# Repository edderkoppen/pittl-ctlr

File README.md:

# pittl-ctlr
Raspberry Pi TTL Controller, 0.2.0  
nGelwan | 2019

## Introduction
PiTTL is a collection of schematics and code which can be used to cheaply build a remotely-controllable random TTL sequence generator using a Raspberry Pi 4 (https://www.raspberrypi.org/products/raspberry-pi-4-model-b/) and a couple of additional hardware components. It consists of two parts, the PiTTL controller, contained in this repository, and the PiTTL client (https://github.com/extradosages/pittl-client). When pushed to the extreme, PiTTL supports generating sequences which run for at least a month consisting of pulses of less than 10ms duration. 

## Installation
### HAT Construction
If you don't have an already constructed PiTTL, one can be constructed relatively cheaply. The hardware for PiTTL has been designed like a Raspberry Pi HAT (https://www.raspberrypi.org/blog/introducing-raspberry-pi-hats/), to live on an auxiliary baord which talks to the Raspberry Pi via its GPIO headers. The schematics for the HAT are detailed in the **board** sub-repo (https://github.com/extradosages/pittl-ctlr/board), and can be viewed with EDA software. I used Eagle (https://www.autodesk.com/products/eagle/overview). The gerber files packaged in the **board** sub-repo can be supplied to a custom PCB-vendor in order to custom print the PCB for the HAT.

### Software Installation
One may install the PiTTL controller software on any Raspberry Pi, although the software has only been tested with the Raspberry Pi 4, and the practical limitation of the TTL driver listed above are given in the context of the hardware on a Raspberry Pi 4. Presumably, the software will function on a variety of operating systems, but certain features have been designed with Raspbian in mind (e.g. automatic start using systemd).

The only software prerequisites for the installation of pittld are python >=3.4, python setuptools, and a C-compiler for the compilation of pigpio. To setup and install the software, a very rudimentary shell script *setup/setup.sh* is provided, which should be run as root. Be warned, the setup script is non-transactional and doesn't try very hard to catch errors, so one should pay attention closely to stdout during the installation. If setup completes successfully, pittld may be started by entering

>*pittld*

at the command-line or-- assuming the installation of the systemd units succeeded-- automatically upon restart of the Raspberry Pi. The logs for pittld can be followed with  

>*journalctl -f -u pittld*

on Raspbian. Confirmation that pittld is running successfully can be found in journalctl or by observing updates on the HAT's LCD.

## Overview
### Usage
PiTTL can be used to stage and then generate individual sequences of TTL pulses, called **programs**. Generating-- also known as **staging**-- a program is a two-step process: first, the **timing** of the program is staged, and then the program's **sequence** is staged. If a sequence has been successfully staged, a program can be **started** and **stopped** at will.

**Timing** is specified with 3 parameters: the **total time**, **exposure fraction**, and **resolution**. Total time is the desired length of the program, exposure fraction is the desired fraction of the program during which TTL-on logic will occur, and resolution is the minimum width of a TTL-on pulse. The resolution parameter is *very* important. It drastically simplifies the algorithm for generating random sequences of pulses satisfying the desired exposure fraction. It is important to note that when these three parameters are supplied to PiTTL, that total time and exposure fraction will be adjusted so that the time spent in TTL-on and TTL-off are both integer multiples of the resolution, and so that they are as close to the values specified as possible. Thus, after staging, timing is converted into the **specified**, **adjusted**, and **digital** domains. The specified timing consists of those floating point values requested, adjusted are those values after adjustment for resolution, and digital are those values in integral units of resolution.

A **sequence** is literally a binary sequence representing the TTL-logic time-series of the program. PiTTL can be induced to randomly generate a sequence based on any valid staged timing. If a sequence has been staged and new timing is then staged, the two are then unrelated, and the staged sequence is purged.

Once a program has been **started**, the timing and the sequence are considered **committed**. New sequences and timing can be staged without interrupting the running program.

PiTTL is capable of evaluating the **progress** and **ETA** of a currently running program, and also **stopping** a program, clearing any committed timings and sequences.

This functionality is implemented via PiTTL controller's python API and publicly via the combination of the PiTTL controller's manager service and the PiTTL client (https://github.com/extradosages/pittl-client).

### Details
The PiTTL controller is organised into several related hardware components and software services. These are the:
1. Manager
2. TTL Driver
3. LCD
4. Connectivity monitor

The software services are packaged under the name **pittld**, for PiTTL Daemon.
#### The Manager
The manager provides a public endpoint for communicating with a PiTTL controller. It is the means by which a PiTTL client can command a PiTTL controller to stage timing and sequences and to start and stop programs, and also the means by which a PiTTL client can query a PiTTL controller for any staged or committed timing or sequences, or the progress of any running program.
#### The TTL Driver
This software service leverages the use of the python library PiGPIO (http://abyz.me.uk/rpi/pigpio/) and a MOSFET to generate the ~4.4V square wave pulses consituting a TTL pulse train.

This software includes the routines to approximately sample from the collection of all subsets of the unit interval with fixed measure without measure-zero components. A resolution parameter (defining the minimum width of a sampled pulse) specifies the accuracy (and memory burden) of the sampling routine, with asymptotic convergence to the ideal sampler upon decreasing the parameter. Once sampled, such a subset defines a pulse train via a mapping of the unit interval onto some interval (probably larger) interval of the time axis. Non-exhaustive testing has determined that *time \* resolution* reaches a practical minimum at ~10^-3 s^2 due to GPIO consdierations and that *time / resolution* reaches a practical maximum at ~0.2 \* 10\^9 due to memory considerations.

This software also contains routines to generate TTL-pulse trains of (ideally) arbitrary frequencey and duty-cycle, but as of 0.2.0 these have not been extensively tested.
#### The LCD
The PiTTL HAT was designed with a HD44780 16colx2row LCD which can convey information about connectivity and program progress without having to use the python API, pittld logs, or PiTTL client.
#### The Connectivity Monitor
The connectivity monitor supplies pittld with information regarding internet connectivity.

## Troubleshooting
If the PiTTL controller is not behaving as expected (usually indicated by oddities displayed on the HAT's LCD), or has encountered an error, the most robust way to fix the problem is to cycle the power on the Raspberry Pi. There has not yet been implemented a robust software means of resetting the pittld service.

Failure of the LCD on the PiTTL HAT should not a be a surprise. The HD44780 is cheap.

It is recommended that the PiTTL controller be installed on a dedicated Raspberry Pi, with a fresh OS. However, if it not the case, it is worth noting that
1. The PiTTL manager service needs to be able to listen on port 5000 in order to receive communications from a PiTTL client.

If problems persist, the software repository should be updated and the service reinstalled. If further problems persist, a fresh Raspbian should be installed.

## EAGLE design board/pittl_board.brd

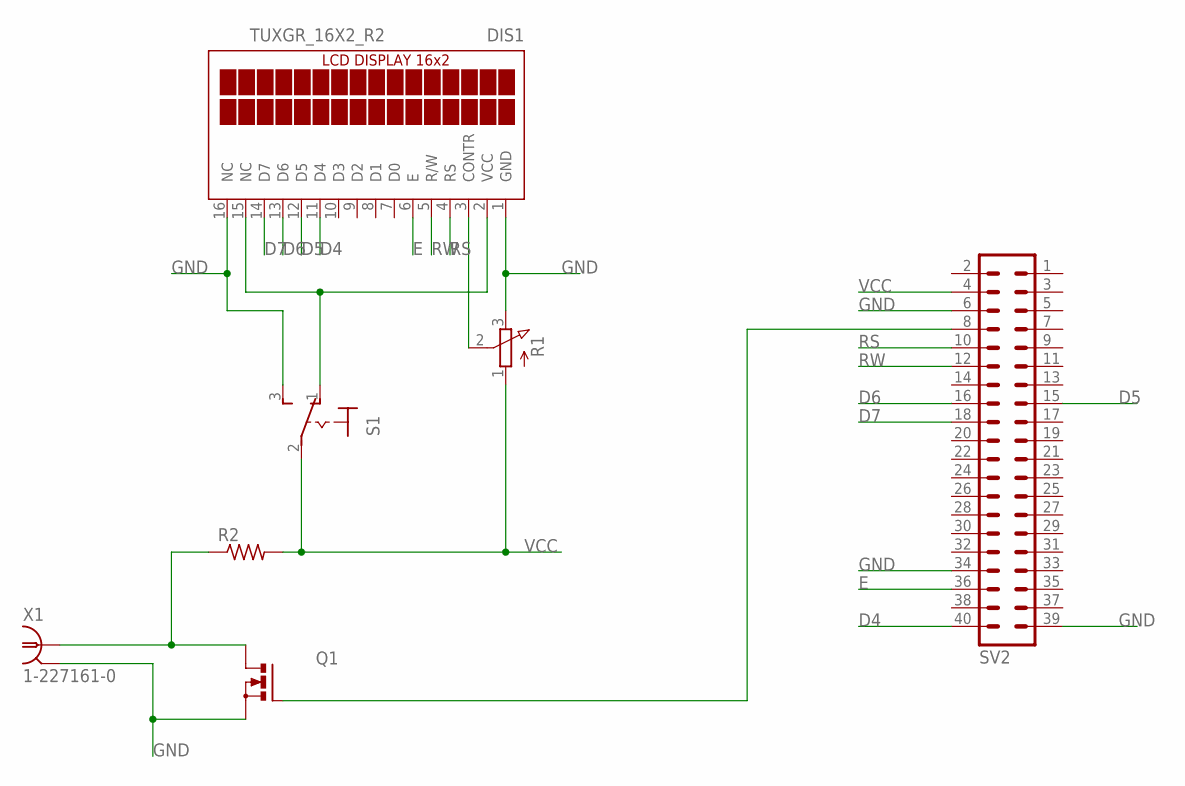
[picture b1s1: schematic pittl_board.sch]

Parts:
DIS1: TUXGR_16X2_R2
Q1: PMOSFET_NTO220BV; TO220BV
R1: 3RP/1610N
R2: R-US_0207/7; 0207/7
S1: 320-916
SV2: MA20-2W
X1: 1-227161-0; AMP_227161

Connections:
D4: DIS1.11 (D4), SV2.40
D5: DIS1.12 (D5), SV2.15
D6: DIS1.13 (D6), SV2.16
D7: DIS1.14 (D7), SV2.18
E: DIS1.6 (E), SV2.36
GND: DIS1.1 (GND), DIS1.16 (NC), Q1.S, R1.3 (E), S1.3 (S), SV2.6, SV2.34, SV2.39, X1.2
unnamed: Q1.G, SV2.8
unnamed: DIS1.2 (VCC), DIS1.15 (NC), S1.1 (O)
unnamed: DIS1.3 (CONTR), R1.2 (S)
unnamed: Q1.D, R2.1, X1.1
RS: DIS1.4 (RS), SV2.10
RW: DIS1.5 (R/W), SV2.12
VCC: R1.1 (A), R2.2, S1.2, SV2.4

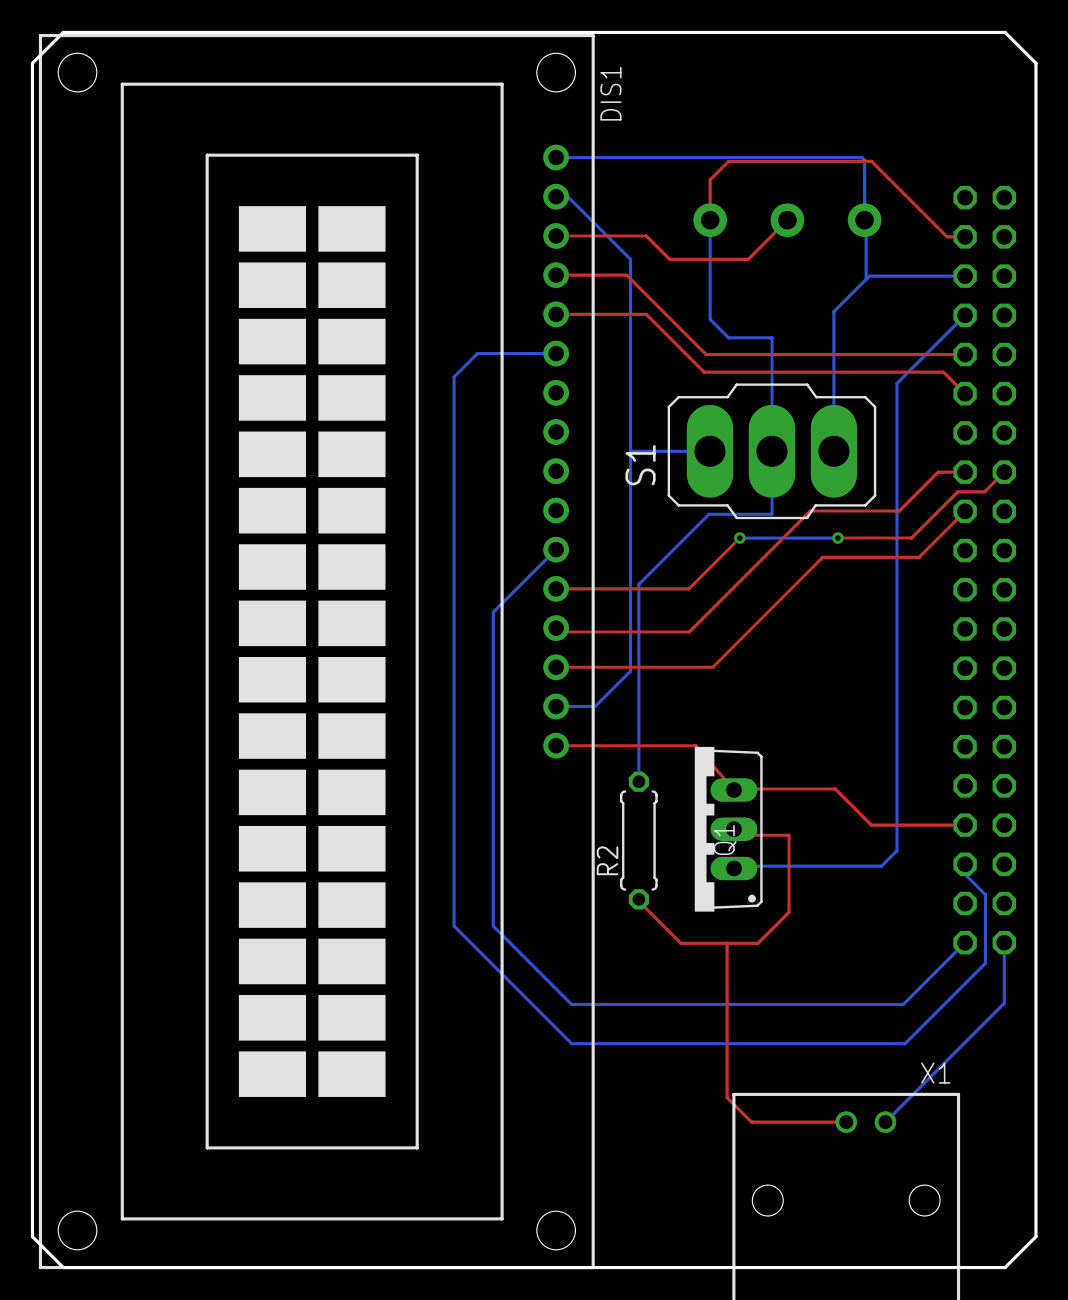
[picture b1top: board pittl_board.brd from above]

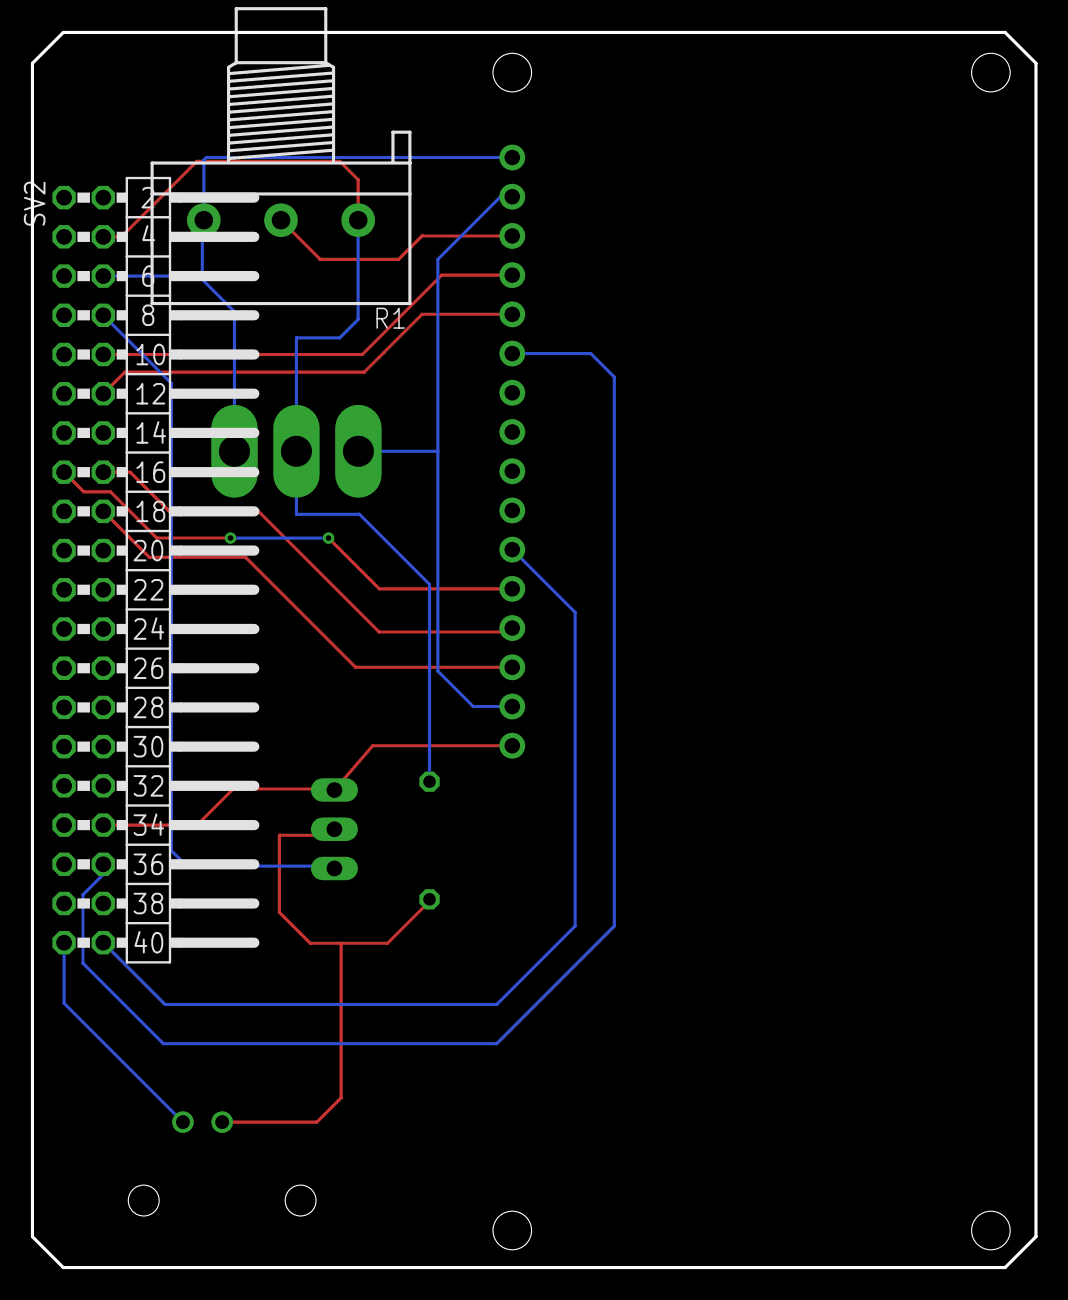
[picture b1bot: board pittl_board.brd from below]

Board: 2 copper layers, 65.0 x 80.0 mm, 7 parts (2 on the bottom side), 13 nets.

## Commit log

2019-10-17 built lcd service
2019-10-17 added services entrypoint
2019-10-17 built internet connectivity monitoring service
2019-10-17 moved statefulness into an object instead of globals
2019-10-21 service model overhaul
2019-10-21 split out the driver service and cli stuff
2019-10-23 removed stupid message passing interface from lcd, simplified its loop. More or less working now
2019-10-28 reworked service api and added cli subpackage
2019-11-04 introduced waveform staging for extended operation, cleaned-up code-base
2019-11-04 added board files
2019-11-04 separated out client, server, shared code
2019-11-04 working cli, project organized
2019-11-04 fixed gitignore
2019-11-13 took client out of repo and flattened it
2019-11-13 Create LICENSE
2019-11-14 added setup.py and moved message formatting here
2019-11-14 added setup
2019-11-14 added sequence transfer
2019-11-14 fixed sequence streaming
2019-11-14 updated streaming protocol for sequences
2019-11-14 touched up sequence transfer
2019-11-17 fixed pigpio not accepting waveforms of given length by reducing waveform length
2019-11-17 Renamed package pittld. Added service MAD
2019-11-17 updated setup.sh
2019-11-17 fixed __main__.py
2019-11-17 added some exits to setup.sh
2019-11-17 fixed setup.sh
2019-11-17 fixed svc.py
2019-11-17 made message passing python primitives
2019-11-17 fixed driver chain indexing error
2020-11-14 Update README.md
    Github username edderkoppen -> extradosages
2022-09-30 chore: add `citation.cff`
2022-09-30 chore: update `CITATION.cff`
